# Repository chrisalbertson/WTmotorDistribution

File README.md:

# WTmotorDistribution -- Wide Thumper chassis motor power and encoder distriution board.

This PCB is very simple.  It is basically a termal block for connecting wires.
But there are six moters with large size wires and this PCB reduces the bulk of wires that must
to lead from the sub chass up to the top plate.   

There is a 3D printable plastic enclosure for this PCB. 
The plastic protects the connections and prevents shorts
Look at it or download here: https://a360.co/3aERoY5

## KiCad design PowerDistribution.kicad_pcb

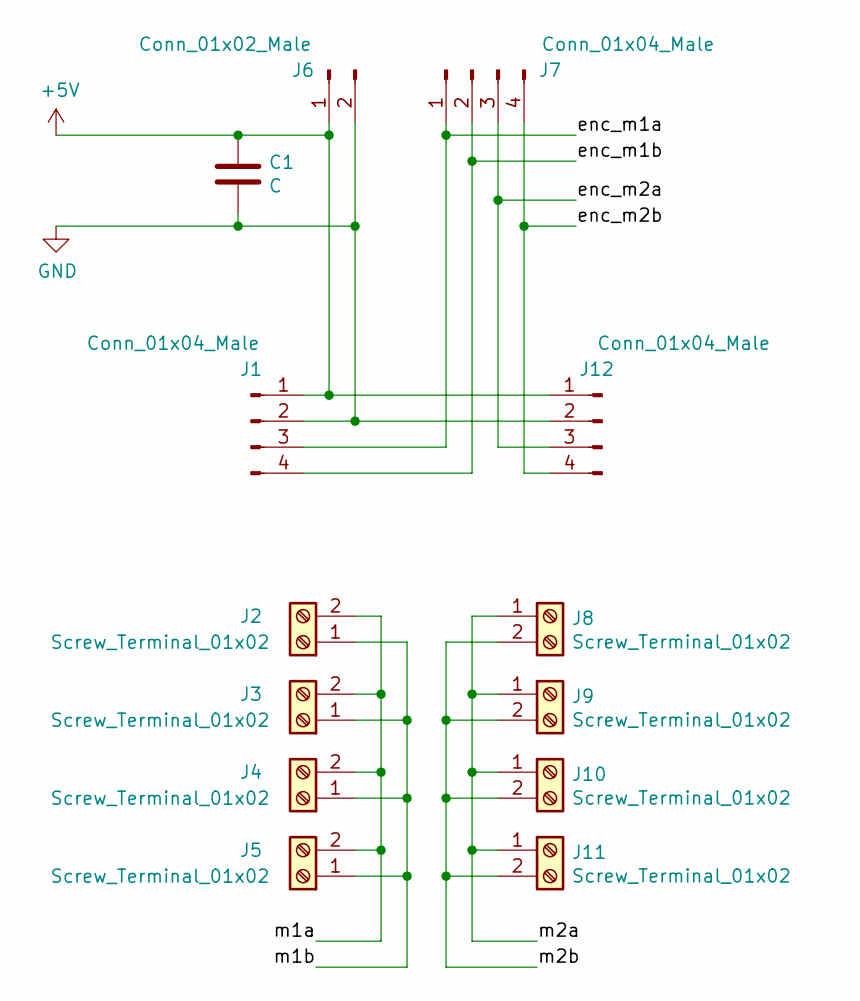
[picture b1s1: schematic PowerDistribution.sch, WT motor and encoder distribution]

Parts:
C1: C; C_Disc_D3.4mm_W2.1mm_P2.50mm
J1, J7, J12: Conn_01x04_Male; PinHeader_1x04_P2.54mm_Horizontal
J2, J3, J4, J5, J8, J9, J10, J11: Screw_Terminal_01x02; SCREWTERMINAL-5MM-2
J6: Conn_01x02_Male; PinHeader_1x02_P2.54mm_Horizontal

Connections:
+5V: C1.1, J1.1, J6.1, J12.1
/enc_m1a: J1.3, J7.1
/enc_m1b: J1.4, J7.2
/enc_m2a: J7.3, J12.3
/enc_m2b: J7.4, J12.4
/m1a: J2.2, J3.2, J4.2, J5.2
/m1b: J2.1, J3.1, J4.1, J5.1
/m2a: J8.1, J9.1, J10.1, J11.1
/m2b: J8.2, J9.2, J10.2, J11.2
GND: C1.2, J1.2, J6.2, J12.2

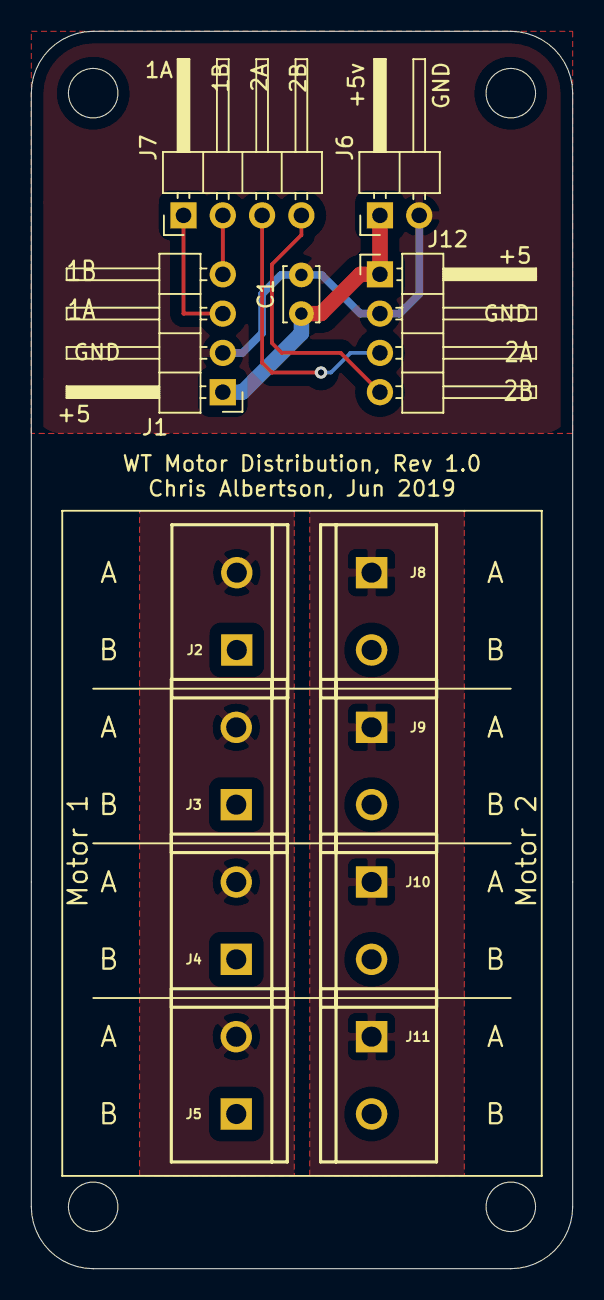
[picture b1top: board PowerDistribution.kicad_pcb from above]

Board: 2 copper layers, 35.0 x 80.0 mm, 13 parts (0 on the bottom side), 10 nets.

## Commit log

2019-06-05 added README
2019-06-05 fixed typos in README
2020-04-27 Update README.md
    Added link to plastic box
